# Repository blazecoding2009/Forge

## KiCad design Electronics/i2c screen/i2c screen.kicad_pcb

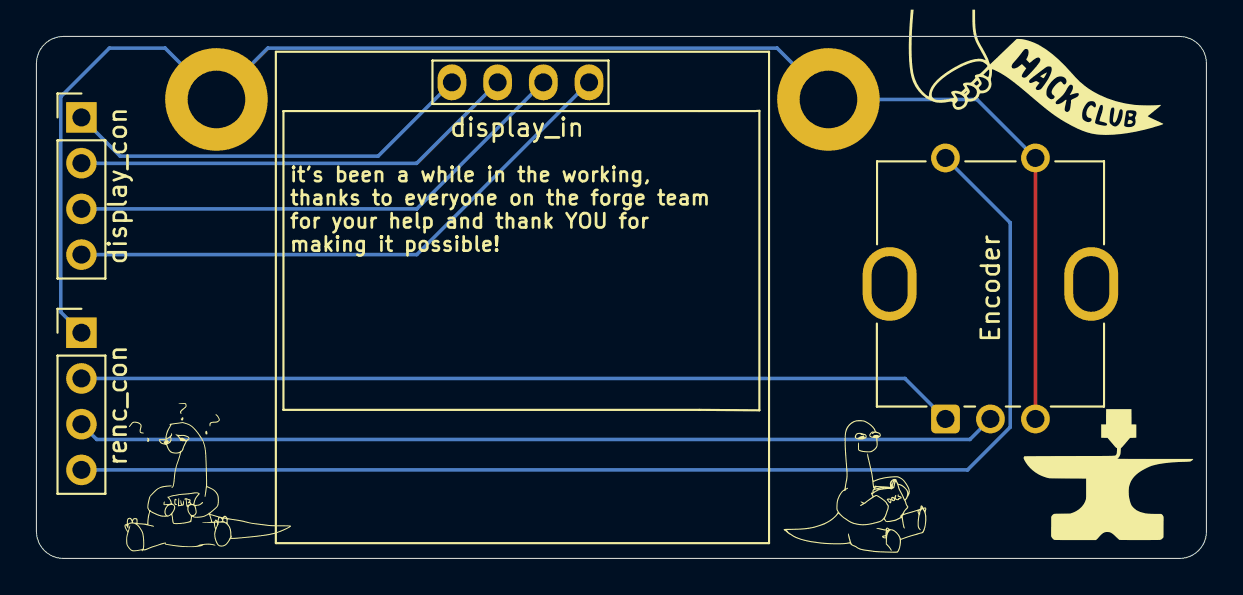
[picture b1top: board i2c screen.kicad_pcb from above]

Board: 2 copper layers, 65.0 x 29.0 mm, 6 parts (0 on the bottom side), 8 nets.

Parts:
H1, H2: MountingHole_3.2mm_M3_ISO7380_Pad
J1: renc_con; PinHeader_1x04_P2.54mm_Vertical
J2: display_con; PinHeader_1x04_P2.54mm_Vertical
J3: display_in; 128x64OLED
SW1: Encoder; RotaryEncoder_Bourns_Vertical_PEC12R-3x17F-Sxxxx

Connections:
EN_BTN: J1.4, SW1.S1
EN_FOR: J1.2, SW1.A
EN_REV: J1.3, SW1.C
GNDREF: H1.1, H2.1, J1.1, SW1.B, SW1.S2
unnamed: J2.2 (3v3), J3.2
unnamed: J2.1 (gnd), J3.1
unnamed: J2.3 (scl), J3.3
unnamed: J2.4 (sda), J3.4

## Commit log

2024-08-18 mounting holes mini scrap
2024-08-18 mounting holes
